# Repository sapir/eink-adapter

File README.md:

# E-Ink adapter board and driver code

See https://hackaday.io/project/7443-e-ink-display-adapter.

This version has grayscale support that depends on some modifications to the
rev. 2 adapter board. Specifically, CKV must be controlled directly by the
microcontroller and not through the shift register. So far I have done this by
breadboarding the shift register and wiring its pins (except CKV) to the
appropriate pins on the board, then wiring CKV separately.

### Previous work and licensing

This is heavily based on previous work:
 * PetteriAimonen [explanations and PCB](http://essentialscrap.com/eink/index.html) (unknown license) and [driver code](https://github.com/PetteriAimonen/ED060SC4_driver) (public domain license)
 * Sprite_tm [explanations and PCB](http://spritesmods.com/?art=einkdisplay) (CC-BY-SA license) and [driver code](http://git.spritesserver.nl/espeink.git/) [(here's a github fork)](https://github.com/take-i/espeink) (beer-ware license)
 * zephray [NekoCal project](https://github.com/nbzwt/NekoCal), in particular the driver code (MIT license)

Additionally, the driver code uses the [esp-open-rtos ESP8266 SDK](https://github.com/Superhouse/esp-open-rtos.git) (various licenses).

As far as I'm concerned, I'd license this repository under the MIT license, but
the PCB may be under CC-BY-SA, and there may be other restrictions if you use
the esp-open-rtos SDK.

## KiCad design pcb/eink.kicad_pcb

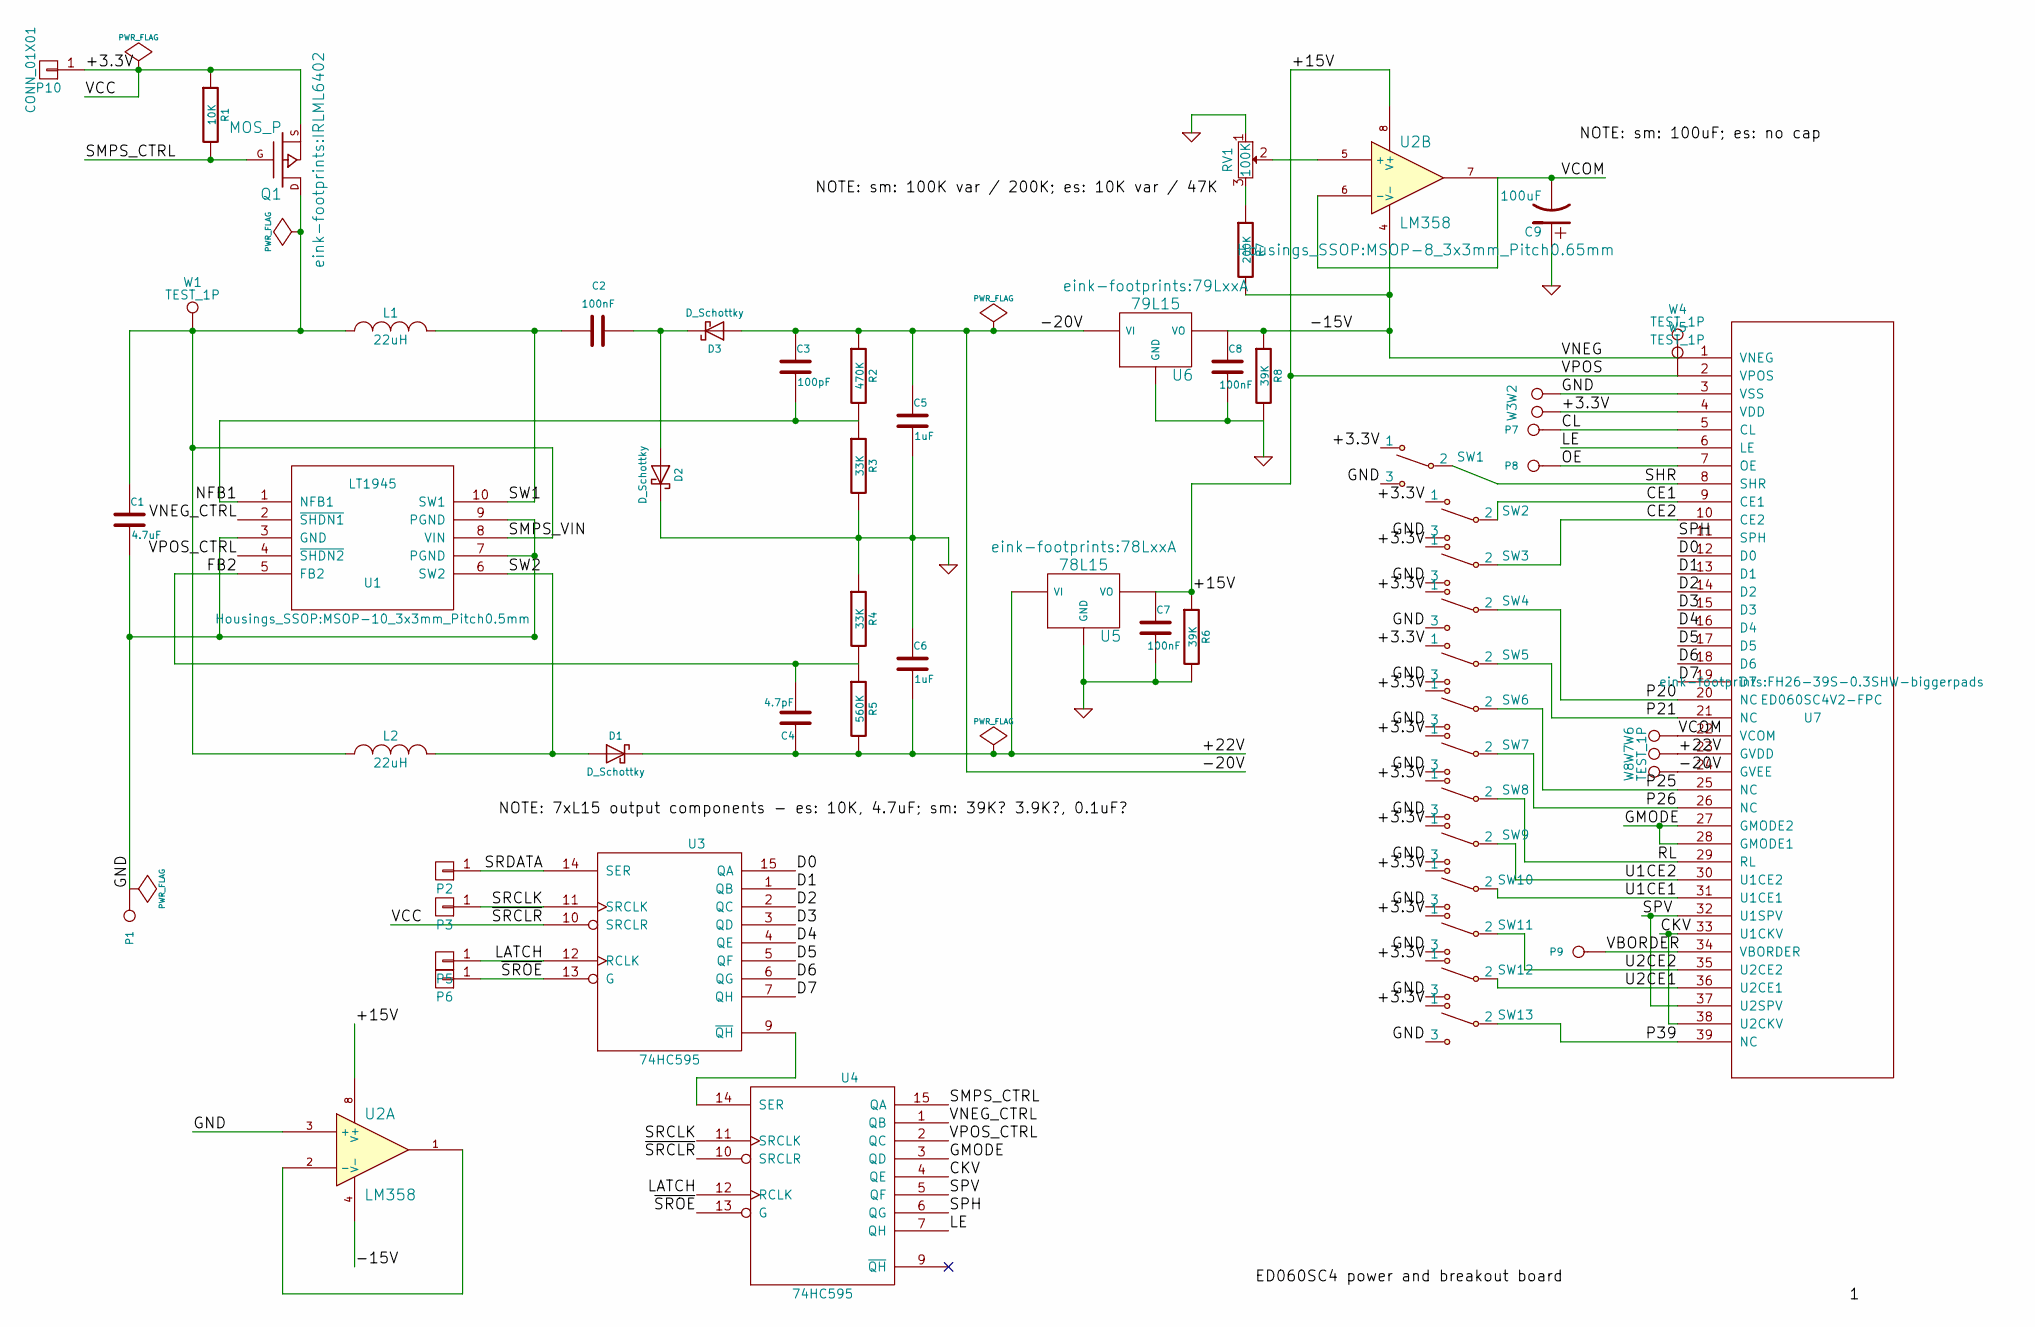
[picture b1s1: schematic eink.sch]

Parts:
C1: 4.7uF; C_0805_HandSoldering
C2, C7, C8: 100nF; C_0805_HandSoldering
C3: 100pF; C_0805_HandSoldering
C4: 4.7pF; C_0805_HandSoldering
C5, C6: 1uF; C_0805_HandSoldering
C9: 100uF; C_Radial_D5_L6_P2.5
D1, D2, D3: D_Schottky; SMB-SMC_Universal_Handsoldering
L1, L2: 22uH; SELF-WE-TPC_M
P1, P7, P8, P9: CONN_1; Pin_Header_Straight_1x01
P2, P3, P5, P6, P10: CONN_01X01; Pin_Header_Straight_1x01
Q1: MOS_P; IRLML6402
R1: 10K; R_0805_HandSoldering
R2: 470K; R_0805_HandSoldering
R3, R4: 33K; R_0805_HandSoldering
R5: 560K; R_0805_HandSoldering
R6, R8: 39K; R_0805_HandSoldering
R7: 200K; R_0805_HandSoldering
RV1: 100K; Bourns_3314G-1-biggerpads
SW1, SW2, SW3, SW4, SW5, SW6, SW7, SW8, SW9, SW10, SW11, SW12, SW13: SW_SPDT_Small; Pin_Header_Straight_1x03
U1: LT1945; MSOP-10_3x3mm_Pitch0.5mm
U2: LM358; MSOP-8_3x3mm_Pitch0.65mm
U3, U4: 74HC595; DIP-16_W7.62mm_LongPads
U5: 78L15; 78LxxA
U6: 79L15; 79LxxA
U7: ED060SC4V2-FPC; FH26-39S-0.3SHW-biggerpads
W1, W2, W3, W4, W5, W6, W7, W8: TEST_1P; Measurement_Point_Round-TH_Big

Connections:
/+15V: C7.1, R6.1, U2.8 (V+), U5.VO, U7.2 (VPOS), W5.1
/+22V: C4.1, C6.2, D1.1 (K), R5.2, U5.VI, U7.23 (GVDD), W7.1
/-15V: C8.1, R7.2, R8.1, U2.4 (V-), U6.VO, U7.1 (VNEG), W4.1
/-20V: C3.1, C5.1, D3.2 (A), R2.1, U6.VI, U7.24 (GVEE), W8.1
/CE1: SW2.2, U7.9 (CE1)
/CE2: SW3.2, U7.10 (CE2)
/CKV: U4.4 (QE), U7.33 (U1CKV), U7.38 (U2CKV)
/CL: P7.1, U7.5 (CL)
/D0: U3.15 (QA), U7.12 (D0)
/D1: U3.1 (QB), U7.13 (D1)
/D2: U3.2 (QC), U7.14 (D2)
/D3: U3.3 (QD), U7.15 (D3)
/D4: U3.4 (QE), U7.16 (D4)
/D5: U3.5 (QF), U7.17 (D5)
/D6: U3.6 (QG), U7.18 (D6)
/D7: U3.7 (QH), U7.19 (D7)
/FB2: C4.2, R4.2, R5.1, U1.5 (FB2)
/GMODE: U4.3 (QD), U7.27 (GMODE2), U7.28 (GMODE1)
/LATCH: P5.1, U3.12 (RCLK), U4.12 (RCLK)
/LE: U4.7 (QH), U7.6 (LE)
/NFB1: C3.2, R2.2, R3.1, U1.1 (NFB1)
/OE: P8.1, U7.7 (OE)
/P20: SW4.2, U7.20 (NC)
/P21: SW5.2, U7.21 (NC)
/P25: SW6.2, U7.25 (NC)
/P26: SW7.2, U7.26 (NC)
/P39: SW13.2, U7.39 (NC)
/RL: SW8.2, U7.29 (RL)
/SHR: SW1.2, U7.8 (SHR)
/SMPS_CTRL: Q1.G, R1.2, U4.15 (QA)
/SMPS_VIN: C1.1, L1.1, L2.1, Q1.D, U1.8 (VIN), W1.1
/SPH: U4.6 (QG), U7.11 (SPH)
/SPV: U4.5 (QF), U7.32 (U1SPV), U7.37 (U2SPV)
/SRCLK: P3.1, U3.11 (SRCLK), U4.11 (SRCLK)
/SRDATA: P2.1, U3.14 (SER)
/SW1: C2.1, L1.2, U1.10 (SW1)
/SW2: D1.2 (A), L2.2, U1.6 (SW2)
/U1CE1: SW10.2, U7.31 (U1CE1)
/U1CE2: SW9.2, U7.30 (U1CE2)
/U2CE1: SW12.2, U7.36 (U2CE1)
/U2CE2: SW11.2, U7.35 (U2CE2)
/VBORDER: P9.1, U7.34 (VBORDER)
/VCOM: C9.2, U2.6 (-), U2.7, U7.22 (VCOM), W6.1
/VNEG_CTRL: U1.2 (~SHDN1~), U4.1 (QB)
/VPOS_CTRL: U1.4 (~SHDN2~), U4.2 (QC)
/~SROE~: P6.1, U3.13 (G), U4.13 (G)
GND: C1.2, C5.2, C6.1, C7.2, C8.2, C9.1, D2.1 (K), P1.1, R3.2, R4.1, R6.2, R8.2, RV1.1, SW1.3, SW2.3, SW3.3, SW4.3, SW5.3, SW6.3, SW7.3, SW8.3, SW9.3, SW10.3, SW11.3, SW12.3, SW13.3, U1.3 (GND), U1.7 (PGND), U1.9 (PGND), U2.3 (+), U3.8 (GND), U4.8 (GND), U5.GND, U6.GND, U7.3 (VSS), W2.1
unnamed: C2.2, D2.2 (A), D3.1 (K)
unnamed: R7.1, RV1.3
unnamed: RV1.2, U2.5 (+)
unnamed: U2.1, U2.2 (-)
unnamed: U3.9 (~QH), U4.14 (SER)
VCC: P10.1, Q1.S, R1.1, SW1.1, SW2.1, SW3.1, SW4.1, SW5.1, SW6.1, SW7.1, SW8.1, SW9.1, SW10.1, SW11.1, SW12.1, SW13.1, U3.10 (SRCLR), U3.16 (VCC), U4.10 (SRCLR), U4.16 (VCC), U7.4 (VDD), W3.1

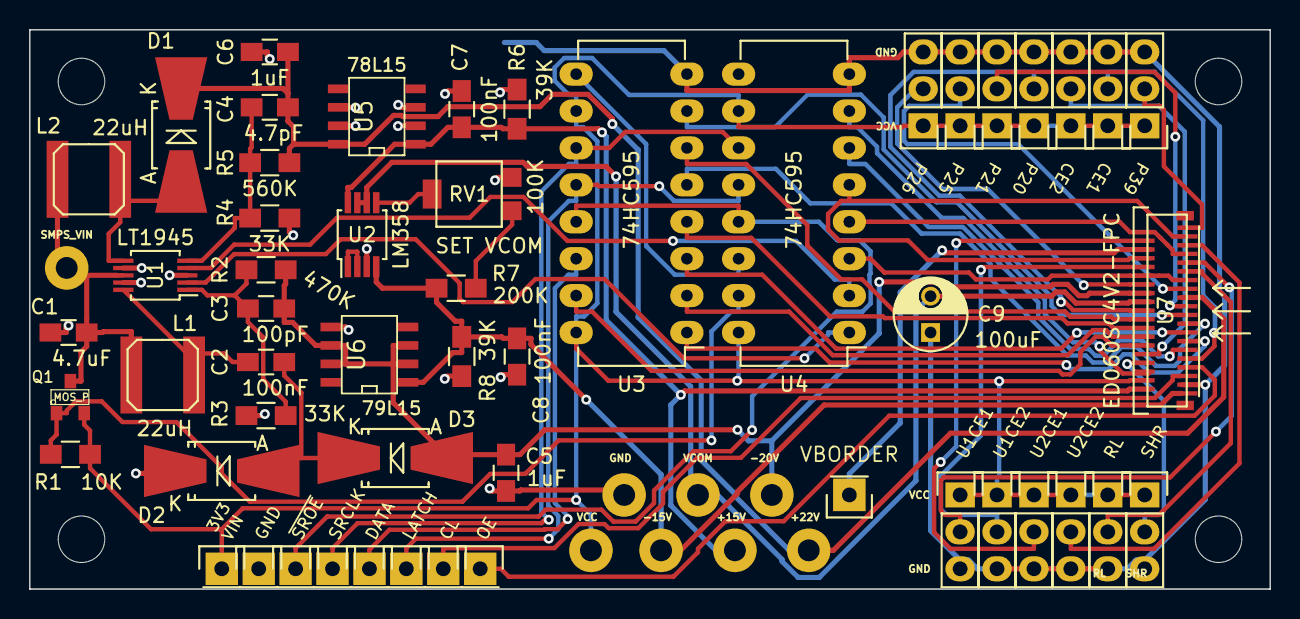
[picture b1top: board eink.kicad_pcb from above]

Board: 2 copper layers, 85.3 x 38.5 mm, 65 parts (0 on the bottom side), 53 nets.

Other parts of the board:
MNT1, MNT2, MNT3, MNT4: MountingHole_3.2mm_M3

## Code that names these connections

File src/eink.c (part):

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#define PIN_CL          PIN_D2      // horizontal clock
// PIN_D1 conflicts with SPI-?
#define PIN_OE          PIN_D3      // display output enable
#define PIN_CKV         PIN_D6
// SPI pins:
//      SRCLK           PIN_D5      // GPIO14
//      DATA            PIN_D7      // GPIO13
//      LATCH           PIN_D8      // GPIO15


// control bits: (low bits belong to shift register, top bits use extra pins)
#define BIT_SMPS        (1<<0)      // SMPS enable, active low
#define BIT_VNEG        (1<<1)      // -20V/-15V enable, active high
#define BIT_VPOS        (1<<2)      // +22V/+15V enable, active high
#define BIT_GMODE       (1<<3)      // GMODE, actually a 2-bit value but we
                                        // tied the 2 bits. 00 is off, 11 is on
#define BIT_SPV         (1<<5)      // start pulse vertical, active low
#define BIT_SPH         (1<<6)      // start pulse horizontal, active low
#define BIT_LE          (1<<7)      // source (horiz.) driver latch enable
#define BIT_CL          (1<<8)      // horizontal clock
#define BIT_OE          (1<<9)      // source (horiz.) driver output enable
                                        // (active high + CKV must be high?)
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{
    gpio_write(PIN_CL, (eink_ctl & BIT_CL) ? 1 : 0);
    gpio_write(PIN_OE, (eink_ctl & BIT_OE) ? 1 : 0);
    gpio_write(PIN_CKV, (eink_ctl & BIT_CKV) ? 1 : 0);
}

static void update_ctl(void)
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
    // high(BIT_OE|BIT_CKV);
    gpio_write(PIN_OE, 1);
    gpio_write(PIN_CKV, 1);
    delay_25ns_steps(high_steps);
    // low(BIT_CKV);
    gpio_write(PIN_CKV, 0);
    delay_25ns_steps(low_steps);
    // low(BIT_OE);
    gpio_write(PIN_OE, 0);
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    gpio_enable(PIN_SR_N_OE, GPIO_OUTPUT);
    gpio_enable(PIN_CL, GPIO_OUTPUT);
    gpio_enable(PIN_OE, GPIO_OUTPUT);
    gpio_enable(PIN_CKV, GPIO_OUTPUT);

    // initialize SR value to turning screen off, then enable the SR output
    eink_ctl = BIT_SMPS;
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
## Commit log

2015-09-29 Add kicad project, schematic and PCB files.
2015-09-29 Add text to back silkscreen.
2015-09-29 Fix up voltage annotation texts (on "drawing" layer).
2015-09-29 Export gerber files.
2015-09-29 Add hackaday.io link to README.
2015-09-30 Rotate (almost all) reference labels by 90 degrees.
2015-09-30 Update gerber files.
2015-10-05 Terminate the LM358's other op-amp.
2015-10-05 Partially rerun routing to fix some DRC violations (caused by manual routing :/ ).
2015-10-18 Fix FPC connector pinout and turn it around to face edge.
2016-04-10 New version of board for new version of KiCad :)
2016-10-19 Revision 2 of board with shift registers.
2016-10-19 Add footprints library.
2016-11-29 Add more KiCAD files.
2016-12-05 Rename eink-kicad/ to pcb/.
2016-12-05 Resave kicad files with a new (?) version, rescued trimpot part.
2016-12-05 Import WIP driver code.
2016-12-05 Ignore *.pyc.
2016-12-06 Update revision on schematic.
2016-12-11 Add SPI pin definitions in a comment.
2016-12-11 Add comments about black/white voltages.
2016-12-11 Redo EPD output code based on NekoCal. Also, fixed delay functions.
2016-12-11 Update README.
2016-12-17 Remove unused include queue.h.
2016-12-31 Split waveform.[ch] from eink.[ch].
2016-12-31 Change bitmap definitions to accomodate different pixel bit sizes.
2016-12-31 Modify vscan_write and hscan_stop to allow multiple vscan_writes for a single hscan.
2016-12-31 Disable GMODE in vscan_stop.
2016-12-31 Reuse refresh hscan for entire screen with multiple vscan_write calls.
2016-12-31 Skip using neutral vscan_writes instead of vclks or stopping vscan.
2016-12-31 Disable interrupts while writing to screen so they don't affect timing.
2017-01-08 Use longer write time for clearing.
2017-01-08 Move recvall, sendall to separate skall.c.
2017-01-08 Split missing API definitions to missing_api.h.
2017-01-08 Use standard C headers instead of c_types.h.
2017-01-08 Add extern "C" to eink.h, waveform.h.
2017-01-08 Inline vscan_write etc. to fix timing.
2017-01-08 Move CKV out of shift register.
2017-01-08 Add stage delay between refresh cycles, less flickery.
2017-01-08 Split waveform.c to wf_refresh.c, wf_update.c.
2017-01-08 Move hclk(2) from end of vscan_write to beginning of hscan_start.
2017-01-08 Remove -Os as it prevents inlining gpio_write. Also -g0 by the way.
2017-01-08 Add waveform stage delay option.
2017-01-08 Longer refresh waveform, existing waveform doesn't entirely clear screen.
2017-01-08 Add compile-time REFRESH_CYCLES option.
2017-01-08 Switch to 4-bit grayscale, with calculated waveforms. (Not wholly correct yet).
2017-01-08 Use NekoCal's update waveform.
2017-01-08 Print free heap size on startup.
2017-01-08 Increase chunk size to 160x200.
2017-01-08 Add note about modifications to rev. 2 board for grayscale.
2017-01-08 Print update waveform for debugging.
2017-01-08 Set chunk overlap to 0.
2017-01-08 Make struct update_waveform so update waveform can be swapped at runtime.
